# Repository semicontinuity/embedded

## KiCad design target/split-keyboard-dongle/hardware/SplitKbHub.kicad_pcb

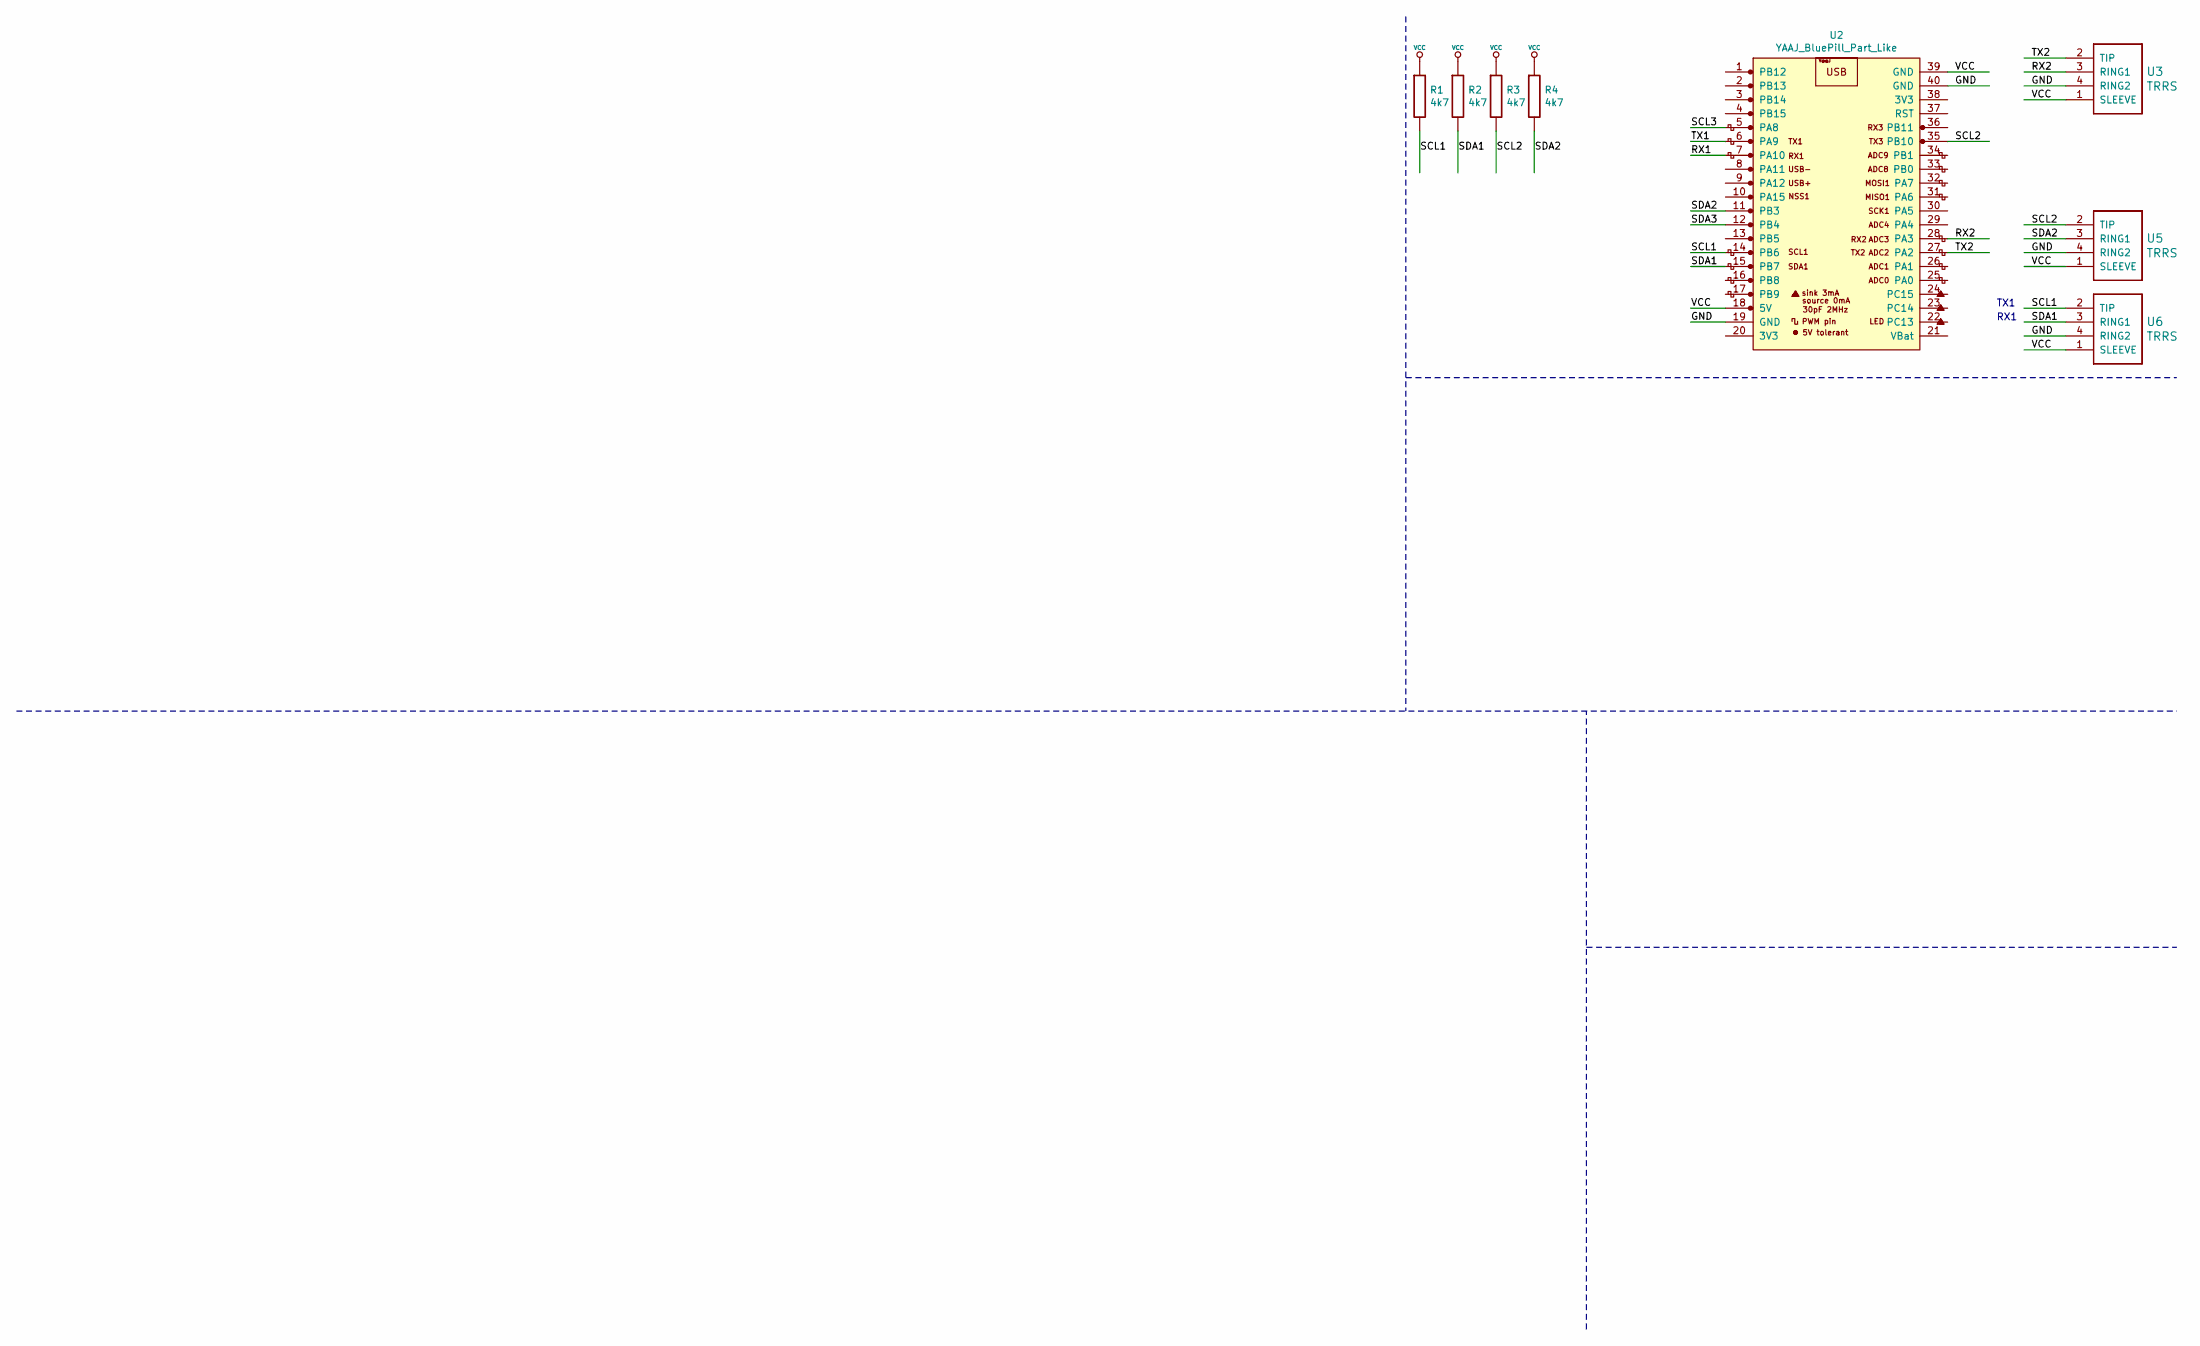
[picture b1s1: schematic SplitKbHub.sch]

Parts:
R1, R2, R3, R4: 4k7; R_0805_2012Metric_Pad1.20x1.40mm_HandSolder
U2: YAAJ_BluePill_Part_Like; YAAJ_BluePill_1
U3, U5, U6: TRRS; TRRS-PJ-320A

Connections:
/GND: U2.19 (GND), U2.40 (GND), U3.4 (RING2), U5.4 (RING2), U6.4 (RING2)
/RX1: U2.7 (PA10)
/RX2: U2.28 (PA3), U3.3 (RING1)
/SCL1: R1.2, U2.14 (PB6), U6.2 (TIP)
/SCL2: R3.2, U2.35 (PB10), U5.2 (TIP)
/SCL3: U2.5 (PA8)
/SDA1: R2.2, U2.15 (PB7), U6.3 (RING1)
/SDA2: R4.2, U2.11 (PB3), U5.3 (RING1)
/SDA3: U2.12 (PB4)
/TX1: U2.6 (PA9)
/TX2: U2.27 (PA2), U3.2 (TIP)
VCC: R1.1, R2.1, R3.1, R4.1, U2.18 (5V), U2.39 (GND), U3.1 (SLEEVE), U5.1 (SLEEVE), U6.1 (SLEEVE)

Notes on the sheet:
TX1
RX1

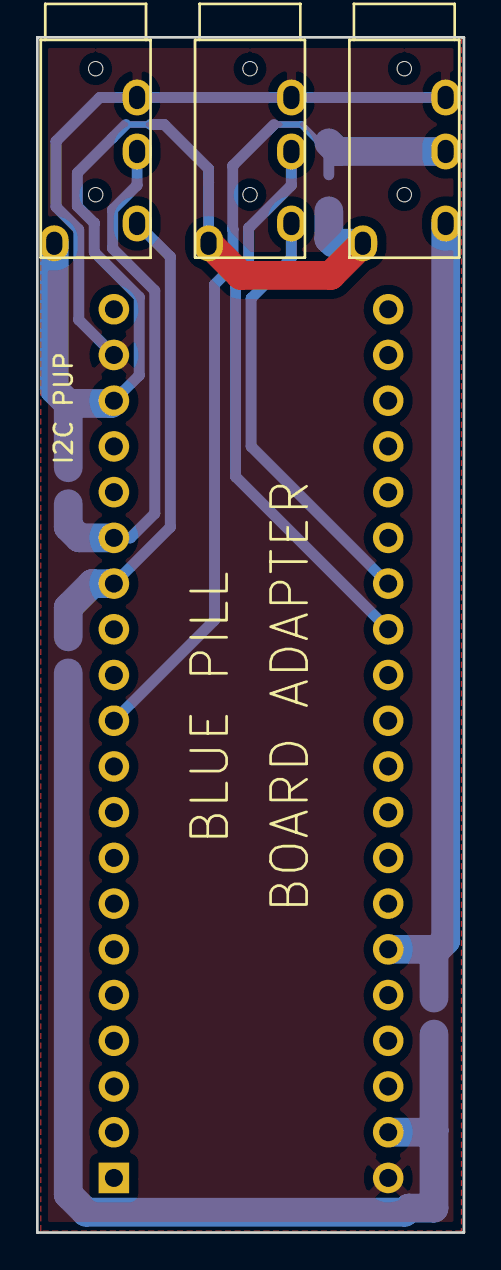
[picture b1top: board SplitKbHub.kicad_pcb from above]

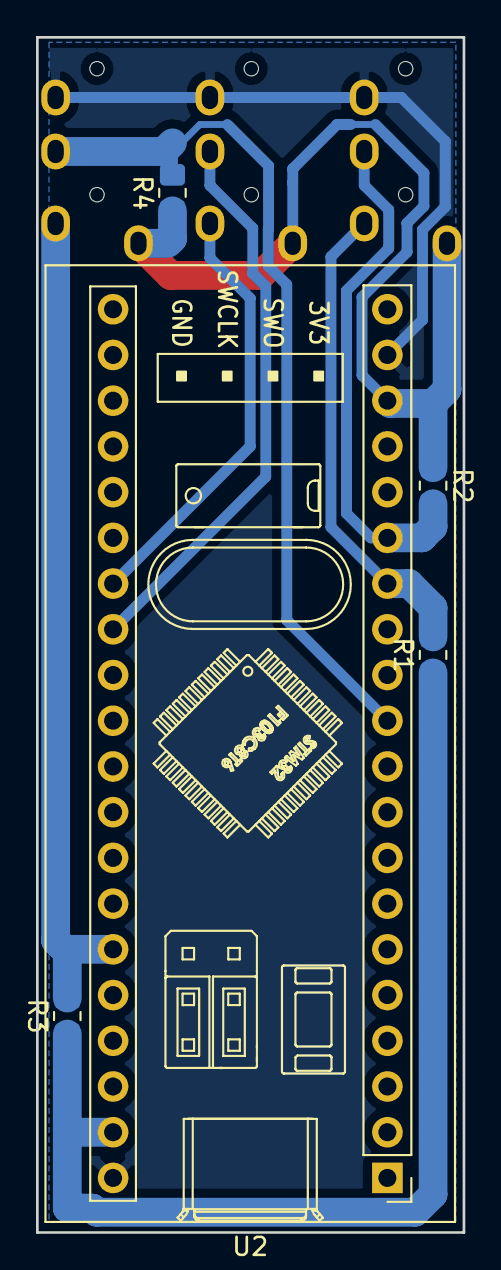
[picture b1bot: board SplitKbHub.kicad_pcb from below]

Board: 2 copper layers, 23.7 x 66.4 mm, 8 parts (5 on the bottom side), 8 nets.
